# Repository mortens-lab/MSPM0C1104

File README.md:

# MSPM0C1104
KiCad and Gerbers files, TI Composer Studio Code

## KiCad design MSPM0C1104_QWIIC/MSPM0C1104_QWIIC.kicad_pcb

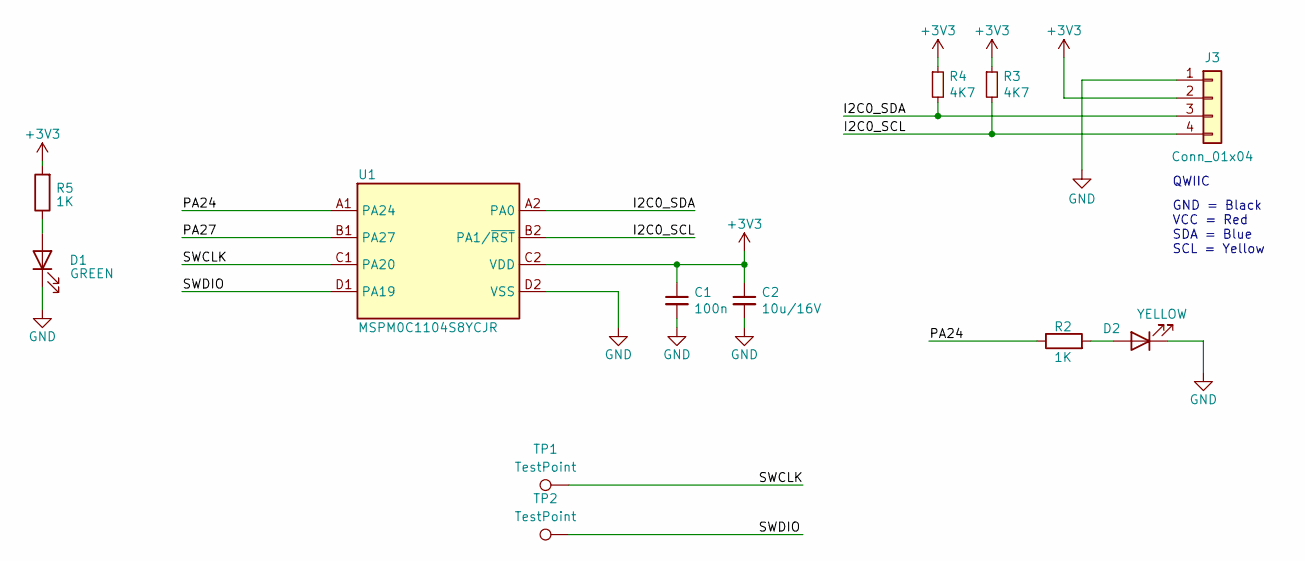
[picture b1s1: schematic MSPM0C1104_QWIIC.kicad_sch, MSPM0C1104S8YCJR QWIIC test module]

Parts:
C1: 100n; C_0402_1005Metric; Part Number GRM155R71H104KE14D; Mouser 81-GRM155R71H104KE4D
C2: 10u/16V; C_0603_1608Metric; Part Number CL21B106KOQNNNE; Mouser 187-CL21B106KOQNNNE
D1: GREEN; LED_0603_1608Metric; Part Number APHD1608LCGCK; Mouser 604-APHD1608LCGCK
D2: YELLOW; LED_0603_1608Metric; Part Number APTD1608LSYCK; Mouser 604-APTD1608LSYCK
J3: Conn_01x04; JST_SH_SM04B-SRSS-TB_1x04-1MP_P1.00mm_Horizontal; Part Number PRT-14417; Digikey 455-SM04B-SRSS-TBCT-ND
R2, R5: 1K; R_0402_1005Metric; Part Number CRCW04021K00FKED; Mouser 71-CRCW0402-1.0K-E3
R3, R4: 4K7; R_0402_1005Metric; Part Number CRCW04024K70FKED; Mouser 71-CRCW0402-4.7K-E3
TP1, TP2: TestPoint; TestPoint_Pad_D1.0mm
U1: MSPM0C1104S8YCJR; Texas_DSBGA-8_0.86x1.6mm_Layout2x4_P0.35mm; Part Number MSPM0C1104S8YCJR; Mouser See link to TI

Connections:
+3V3: C1.1, C2.1, J3.2, R3.1, R4.1, R5.2, U1.C2 (VDD)
/I2C0_SCL: J3.4, R3.2, U1.B2 (PA1/~RST)
/I2C0_SDA: J3.3, R4.2, U1.A2 (PA0)
/PA24: R2.1, U1.A1 (PA24)
/PA27: U1.B1 (PA27)
/SWCLK: TP1.1, U1.C1 (PA20)
/SWDIO: TP2.1, U1.D1 (PA19)
GND: C1.2, C2.2, D1.1 (K), D2.1 (K), J3.1, J3.MP, U1.D2 (VSS)
unnamed: D1.2 (A), R5.1
unnamed: D2.2 (A), R2.2

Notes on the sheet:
GND = Black VCC = Red SDA = Blue SCL = Yellow
QWIIC

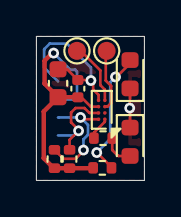
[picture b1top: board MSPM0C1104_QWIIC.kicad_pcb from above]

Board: 2 copper layers, 6.0 x 8.0 mm, 12 parts (1 on the bottom side), 9 nets.

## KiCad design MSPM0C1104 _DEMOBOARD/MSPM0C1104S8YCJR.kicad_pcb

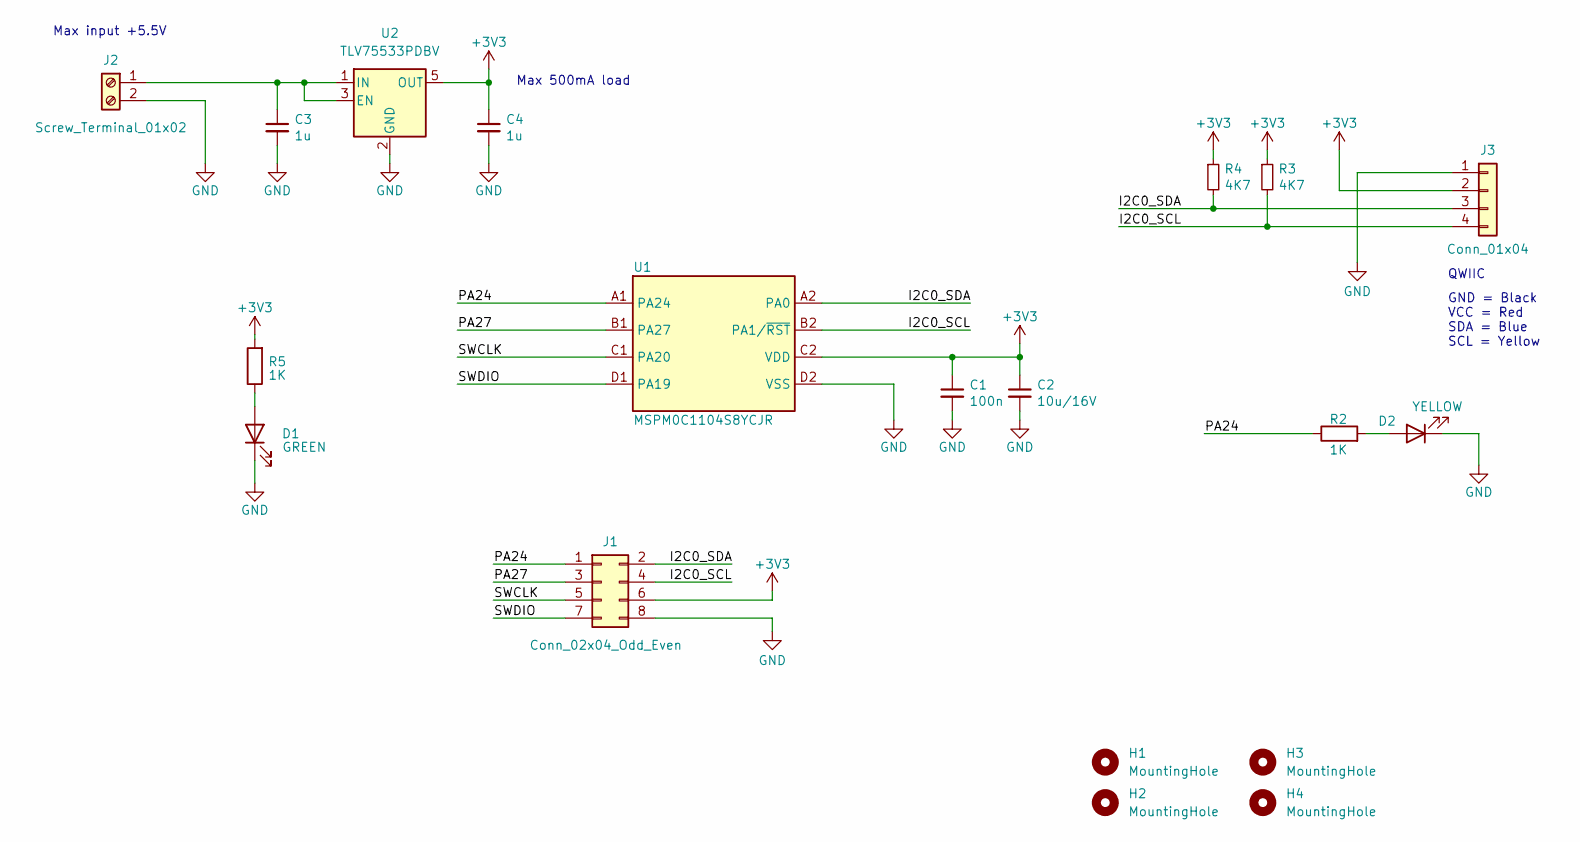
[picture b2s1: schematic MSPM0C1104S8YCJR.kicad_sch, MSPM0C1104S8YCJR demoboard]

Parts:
C1: 100n; C_0402_1005Metric; Part Number GRM155R71H104KE14D; Mouser 81-GRM155R71H104KE4D
C2: 10u/16V; C_0603_1608Metric; Part Number CL21B106KOQNNNE; Mouser 187-CL21B106KOQNNNE
C3, C4: 1u; C_0603_1608Metric; Part Number CL10A105KO8NNNC; Mouser 187-CL10A105KO8NNNC
D1: GREEN; LED_0603_1608Metric; Part Number APHD1608LCGCK; Mouser 604-APHD1608LCGCK
D2: YELLOW; LED_0603_1608Metric; Part Number APTD1608LSYCK; Mouser 604-APTD1608LSYCK
H1, H2, H3, H4: MountingHole; MountingHole_2.7mm; Part Number DNP; Mouser DNP
J1: Conn_02x04_Odd_Even; PinHeader_2x04_P2.54mm_Vertical; Part Number Standard 2x4 - 2.54mm pinheader
J2: Screw_Terminal_01x02; TerminalBlock_Phoenix_PT-1,5-2-3.5-H_1x02_P3.50mm_Horizontal; Part Number 1984617; Mouser 651-1984617
J3: Conn_01x04; JST_SH_SM04B-SRSS-TB_1x04-1MP_P1.00mm_Horizontal; Part Number PRT-14417; Digikey 455-SM04B-SRSS-TBCT-ND
R2, R5: 1K; R_0402_1005Metric; Part Number CRCW04021K00FKED; Mouser 71-CRCW0402-1.0K-E3
R3, R4: 4K7; R_0402_1005Metric; Part Number CRCW04024K70FKED; Mouser 71-CRCW0402-4.7K-E3
U1: MSPM0C1104S8YCJR; Texas_DSBGA-8_0.86x1.6mm_Layout2x4_P0.35mm; Part Number MSPM0C1104S8YCJR; Mouser See link to TI
U2: TLV75533PDBV; SOT-23-5; Part Number TLV75533PDBV; Mouser 595-TLV75533PDBVR

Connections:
+3V3: C1.1, C2.1, C4.1, J1.6, J3.2, R3.1, R4.1, R5.2, U1.C2 (VDD), U2.5 (OUT)
/I2C0_SCL: J1.4, J3.4, R3.2, U1.B2 (PA1/~RST)
/I2C0_SDA: J1.2, J3.3, R4.2, U1.A2 (PA0)
/PA24: J1.1, R2.1, U1.A1 (PA24)
/PA27: J1.3, U1.B1 (PA27)
/SWCLK: J1.5, U1.C1 (PA20)
/SWDIO: J1.7, U1.D1 (PA19)
GND: C1.2, C2.2, C3.2, C4.2, D1.1 (K), D2.1 (K), J1.8, J2.2, J3.1, U1.D2 (VSS), U2.2 (GND)
unnamed: D1.2 (A), R5.1
unnamed: D2.2 (A), R2.2
unnamed: C3.1, J2.1, U2.1 (IN), U2.3 (EN)

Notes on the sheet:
Max input +5.5V
GND = Black VCC = Red SDA = Blue SCL = Yellow
QWIIC
Max 500mA load

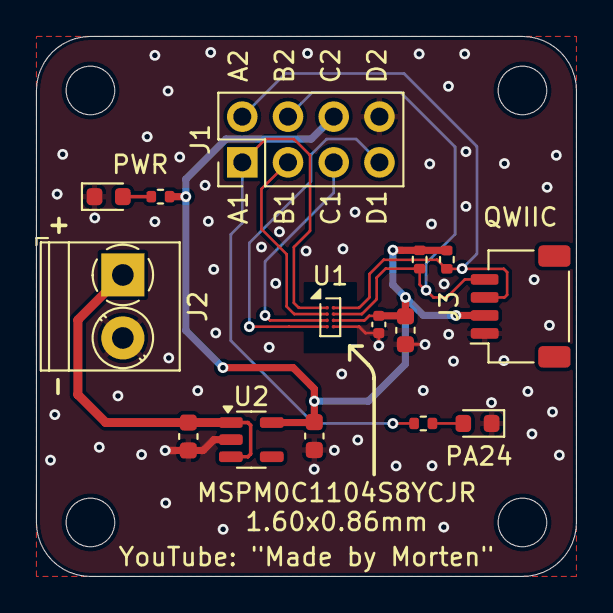
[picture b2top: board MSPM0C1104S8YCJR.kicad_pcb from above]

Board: 2 copper layers, 30.0 x 30.0 mm, 19 parts (0 on the bottom side), 11 nets.

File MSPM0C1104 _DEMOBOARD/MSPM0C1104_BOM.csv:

Qty,Reference,Value,Footprint,Part Number,Manufacturer,Mouser
1,U1,MSPM0C1104S8YCJR,Morten_Library:Texas_DSBGA-8_0.86x1.6mm_Layout2x4_P0.35mm,MSPM0C1104S8YCJR,Texas Instruments,See link to TI
1,U2,TLV75533PDBV,Package_TO_SOT_SMD:SOT-23-5,TLV75533PDBV,Texas Instruments,595-TLV75533PDBVR 
1,C1,100n,Capacitor_SMD:C_0402_1005Metric,GRM155R71H104KE14D,Murata,81-GRM155R71H104KE4D
1,C2,10u/16V,Capacitor_SMD:C_0603_1608Metric,CL21B106KOQNNNE,Samsung,187-CL21B106KOQNNNE
2,"C3,C4",1u,Capacitor_SMD:C_0603_1608Metric,CL10A105KO8NNNC,Samsung,187-CL10A105KO8NNNC
1,D1,GREEN,LED_SMD:LED_0603_1608Metric,APHD1608LCGCK,Kingbright,604-APHD1608LCGCK
1,D2,YELLOW,LED_SMD:LED_0603_1608Metric,APTD1608LSYCK,Kingbright,604-APTD1608LSYCK
4,"H1,H2,H3,H4",MountingHole,MountingHole:MountingHole_2.7mm,DNP,DNP,DNP
1,J1,Conn_02x04_Odd_Even,Connector_PinHeader_2.54mm:PinHeader_2x04_P2.54mm_Vertical,Standard 2x4 - 2.54mm pinheader,-,-
1,J2,Screw_Terminal_01x02,"TerminalBlock_Phoenix:TerminalBlock_Phoenix_PT-1,5-2-3.5-H_1x02_P3.50mm_Horizontal",1984617,Phoenix Contact,651-1984617
1,J3,Conn_01x04,Connector_JST:JST_SH_SM04B-SRSS-TB_1x04-1MP_P1.00mm_Horizontal,PRT-14417,Sparkfun,474-PRT-14417
2,"R2,R5",1K,Resistor_SMD:R_0402_1005Metric,CRCW04021K00FKED,Vishay,71-CRCW0402-1.0K-E3
2,"R3,R4",4K7,Resistor_SMD:R_0402_1005Metric,CRCW04024K70FKED,Vishay,71-CRCW0402-4.7K-E3

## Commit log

2025-04-13 Initial upload
